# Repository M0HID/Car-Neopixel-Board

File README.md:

# L12

A WLED controller for automotive use, in a small, compact form factor!
<!--  -->
(Check out WLED [here](https://github.com/wled/WLED)!)
## ⚙️ Features:
- < 50x50mm total footprint
- Onboard ESP32
- USB-C for both power and flashing
- JTAG pins broken out
- 4 sets of outputs for 4 seperate strips
- Onboard XL4015 buck converter to convert 12V -> 5V

## 🔧 Installation:
1. In a web browser, open https://install.wled.me/
2. Bridge the `boot` solder jumper using a paperclip, then plug it into your computer
3. Press `install` on the webpage, select the ESP32 Device, and follow the instructions there!

## 📷 Gallery
Check out the PCB on [KiCanvas](https://kicanvas.org/?github=https%3A%2F%2Fgithub.com%2FM0HID%2FCar-Neopixel-Board)!
| Description | Image |
|------------|--------|
| PCB Front |  |
|||
| PCB Back |  |
||
| Board full |  |

## 🔢 BOM
The boards are designed so that one can be installed in all 4 doors of the car, with the final one going in the dashboard as the 'Master' controller

### Capacitors

| Item | Quantity x5 | Part Number | Supplier / Link | Price |
|------|------------|------------|----------------|-------|
| 100 nF capacitor | 3 | C1591 | [link](https://www.lcsc.com/product-detail/C1591.html) | 0.26 |
| 1 µF capacitor | 3 | C15849 | [link](https://www.lcsc.com/product-detail/C15849.html) | 0.25 |
| 22 µF capacitor | 2 | C86295 | [link](https://www.lcsc.com/product-detail/C86295.html) | 0.15 |
| 220 µF capacitor | 1 | C125977 | [link](https://www.lcsc.com/product-detail/C125977.html) | 1.04 |
| 330 µF capacitor | 1 | C249985 | [link](https://www.lcsc.com/product-detail/C249985.html) | 1.57 |

### Resistors

| Item | Quantity x5 | Part Number | Supplier / Link | Price |
|------|------------|------------|----------------|-------|
| 5.1 kΩ resistor | 2 | C23186 | [link](https://www.lcsc.com/product-detail/C23186.html) | 0.11 |
| 10 kΩ resistor | 1 | C25804 | [link](https://www.lcsc.com/product-detail/C25804.html) | 0.10 |
| 22 Ω resistor | 2 | C23345 | [link](https://www.lcsc.com/product-detail/C23345.html) | 0.10 |
| 62 Ω resistor | 4 | C23222 | [link](https://www.lcsc.com/product-detail/C23222.html) | 0.12 |
| 1 kΩ resistor | 1 | C21190 | [link](https://www.lcsc.com/product-detail/C21190.html) | 0.10 |
| 3.3 kΩ resistor | 1 | C22978 | [link](https://www.lcsc.com/product-detail/C22978.html) | 0.11 |

### Diodes

| Item | Quantity x5 | Part Number | Supplier / Link | Price |
|------|------------|------------|----------------|-------|
| SS54 Schottky diode | 3 | C22452 | [link](https://www.lcsc.com/product-detail/C22452.html) | 0.87 |

### Inductors

| Item | Quantity x5 | Part Number | Supplier / Link | Price |
|------|------------|------------|----------------|-------|
| APH1265 inductor | 1 | C5349639 | [link](https://www.lcsc.com/product-detail/C5349639.html) | 2.00 |

### Connectors

| Item | Quantity x5 | Part Number | Supplier / Link | Price |
|------|------------|------------|----------------|-------|
| USB Type-C port | 1 | C165948 | [link](https://www.lcsc.com/product-detail/C165948.html) | 0.88 |
| 2-pin terminal block | 4 | C709041 | [link](https://www.lcsc.com/product-detail/C709041.html) | 3.67 |

### ICs / Modules

| Item | Quantity x5 | Part Number | Supplier / Link | Price |
|------|------------|------------|----------------|-------|
| Level shifter | 1 | C2675672 | [link](https://www.lcsc.com/product-detail/C2675672.html) | 5.73 |
| Buck converter | 1 | C51661 | [link](https://www.lcsc.com/product-detail/C51661.html) | 3.27 |
| Voltage regulator | 1 | C6186 | [link](https://www.lcsc.com/product-detail/C6186.html) | 0.83 |
| ESP32 module | 1 | C2913199 | [link](https://www.lcsc.com/product-detail/C2913199.html) | 25.97 |

### LEDs

| Item | Quantity | Supplier / Link | Price | Notes |
|------|----------|----------------|-------|-------|
| Full Colors 90 cm LED strip | 4 | [link](https://www.aliexpress.com/item/1005004940479033.html) | 28.32 |  |
| Full Colors 110 cm LED strip | 1 | [link](https://www.aliexpress.com/item/1005004940479033.html) | 7.71 |  |
| Full Colors LED strip pack (alternative) | 6 | – | 34.50 | Includes 4×75 cm, 1×90 cm, 1×25 cm (driver side dashboard) |

### PCB (JLCPCB)

| Item | Quantity | Supplier / Link | Price | Notes |
|------|----------|----------------|-------|-------|
| PCB | 5 | [JLCPCB](https://jlcpcb.com) | 3.50 | Standard options for 2-layer board |

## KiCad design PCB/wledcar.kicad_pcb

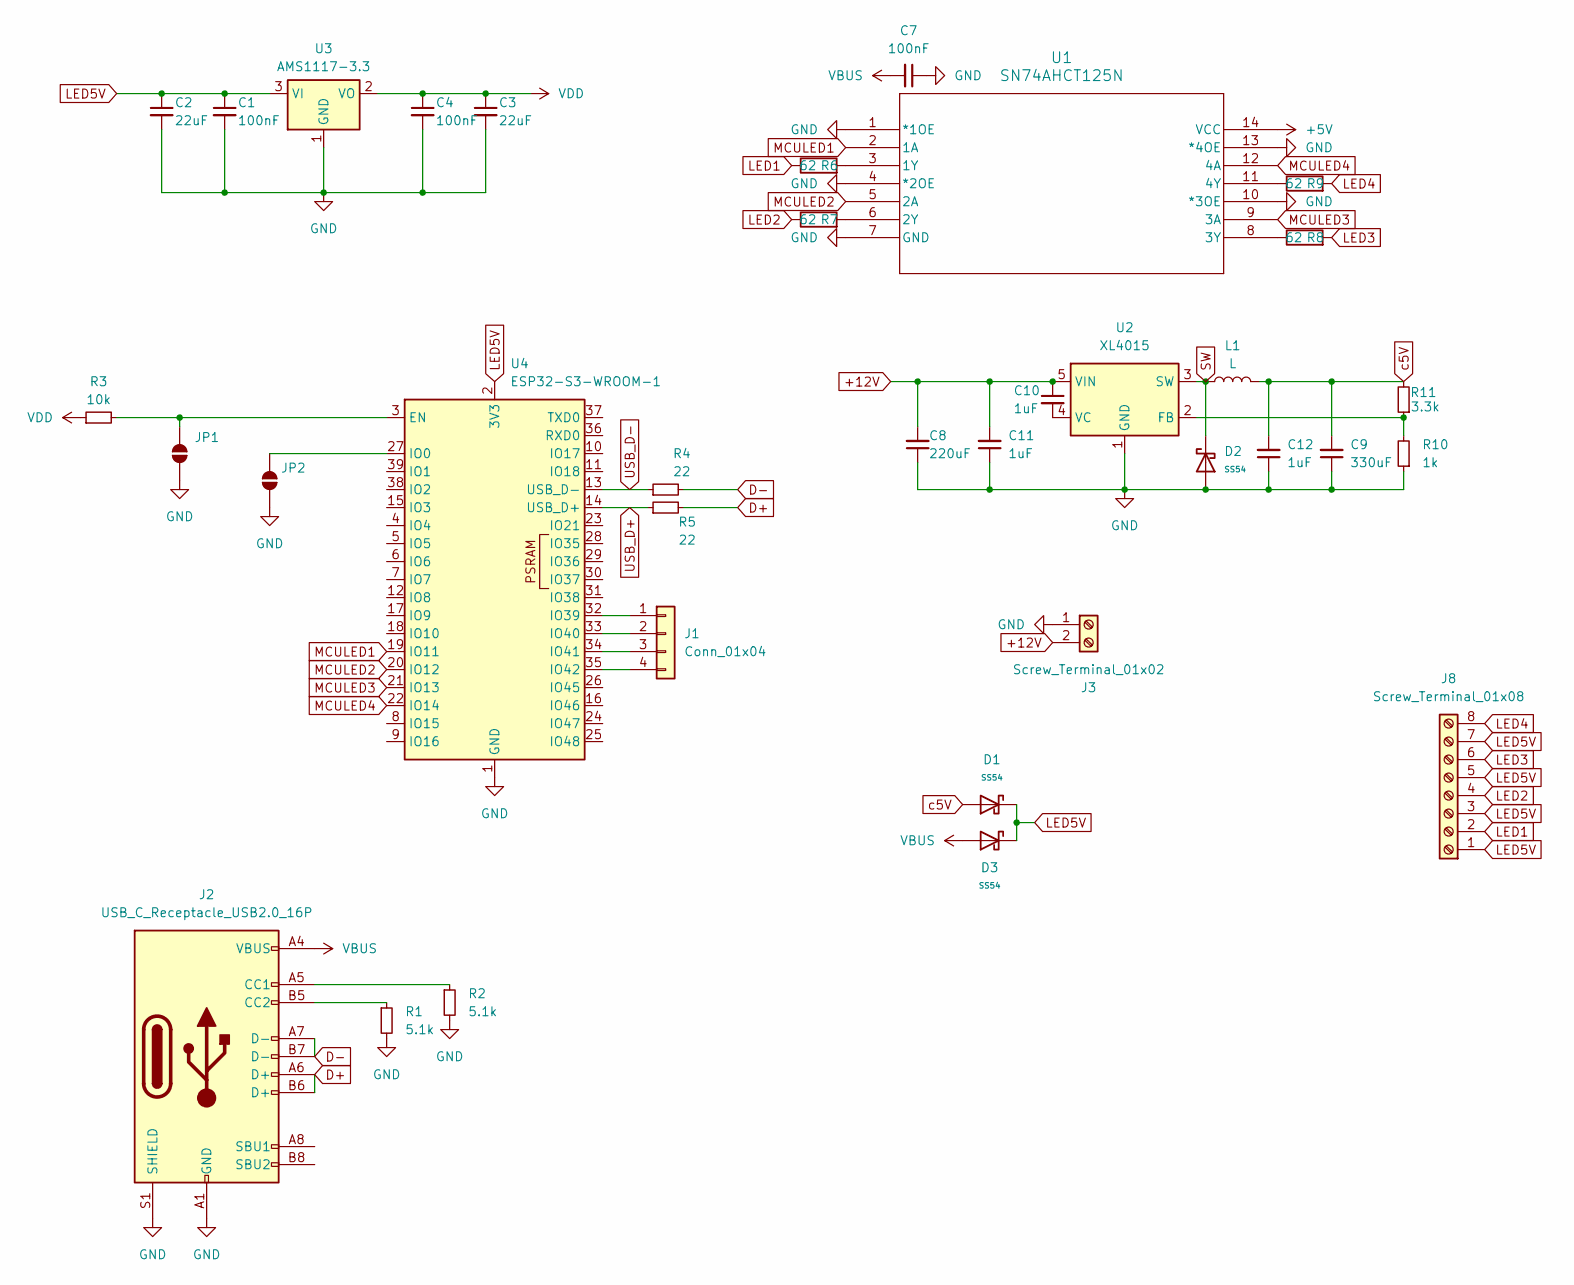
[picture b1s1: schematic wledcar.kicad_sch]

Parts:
C1, C4, C7: 100nF; C_0603_1608Metric
C2, C3: 22uF; C_0603_1608Metric
C8: 220uF; C_0603_1608Metric
C9: 330uF; C_0603_1608Metric
C10, C11, C12: 1uF; C_0603_1608Metric
D1, D2, D3: SS54; D_SMA; Forward Voltage (Vf@If) 550mV@5A; Reverse Voltage (Vr) 40V; Part SS54; LCSC C22452
J1: Conn_01x04; PinHeader_1x04_P1.27mm_Vertical
J2: USB_C_Receptacle_USB2.0_16P; USB_C_Receptacle_HRO_TYPE-C-31-M-12
J3: Screw_Terminal_01x02; TerminalBlock_Phoenix_MKDS-1,5-2-5.08_1x02_P5.08mm_Horizont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
J8: Screw_Terminal_01x08; TerminalBlock_Phoenix_MKDS-3-8-5.08_1x08_P5.08mm_Horizontal
JP1, JP2: SJ2_OPEN; SolderJumper-2_P1.3mm_Open_RoundedPad1.0x1.5mm
L1: L; L_APV_APH1265
R1, R2: 5.1k; R_0603_1608Metric
R3: 10k; R_0603_1608Metric
R4, R5: 22; R_0603_1608Metric
R6, R7, R8, R9: 62; R_0603_1608Metric
R10: 1k; R_0603_1608Metric
R11: 3.3k; R_0603_1608Metric
U1: SN74AHCT125N; SOIC-14_3.9x8.7mm_P1.27mm
U2: XL4015; TO-263-5_TabPin3
U3: AMS1117-3.3; SOT-223-3_TabPin2
U4: ESP32-S3-WROOM-1

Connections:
+5V: U1.14 (VCC)
+12V: C8.2, C10.1, C11.2, J3.2, U2.5 (VIN)
D+: J2.A6 (D+), J2.B6 (D+), R5.2
D-: J2.A7 (D-), J2.B7 (D-), R4.2
GND: C1.2, C2.2, C3.2, C4.2, C7.1, C8.1, C9.1, C11.1, C12.1, D2.2, J2.A1 (GND), J2.A12 (GND), J2.B1 (GND), J2.B12 (GND), J2.S1 (SHIELD), J3.1, JP1.1 (A), JP2.1 (A), R1.2, R2.2, R10.1, U1.1 (*1OE), U1.4 (*2OE), U1.7 (GND), U1.10 (*3OE), U1.13 (*4OE), U2.1 (GND), U3.1 (GND), U4.1 (GND), U4.40 (GND), U4.41 (GND)
LED1: J8.2, R6.1
LED2: J8.4, R7.1
LED3: J8.6, R8.2
LED4: J8.8, R9.2
LED5V: C1.1, C2.1, D1.1, D3.1, J8.1, J8.3, J8.5, J8.7, U3.3 (VI), U4.2 (3V3)
MCULED1: U1.2 (1A), U4.19 (IO11)
MCULED2: U1.5 (2A), U4.20 (IO12)
MCULED3: U1.9 (3A), U4.21 (IO13)
MCULED4: U1.12 (4A), U4.22 (IO14)
unnamed: J1.1, U4.32 (IO39)
unnamed: J1.2, U4.33 (IO40)
unnamed: J1.3, U4.34 (IO41)
unnamed: J1.4, U4.35 (IO42)
unnamed: J2.A5 (CC1), R2.1
unnamed: J2.B5 (CC2), R1.1
unnamed: JP1.2 (B), R3.2, U4.3 (EN)
unnamed: JP2.2 (B), U4.27 (IO0)
unnamed: R6.2, U1.3 (1Y)
unnamed: R7.2, U1.6 (2Y)
unnamed: R8.1, U1.8 (3Y)
unnamed: R9.1, U1.11 (4Y)
unnamed: R10.2, R11.1, U2.2 (FB)
unnamed: C10.2, U2.4 (VC)
SW: D2.1, L1.1, U2.3 (SW)
USB_D+: R5.1, U4.14 (USB_D+)
USB_D-: R4.1, U4.13 (USB_D-)
VBUS: C7.2, D3.2, J2.A4 (VBUS), J2.A9 (VBUS), J2.B4 (VBUS), J2.B9 (VBUS)
VDD: C3.1, C4.1, R3.1, U3.2 (VO)
c5V: C9.2, C12.2, D1.2, L1.2, R11.2

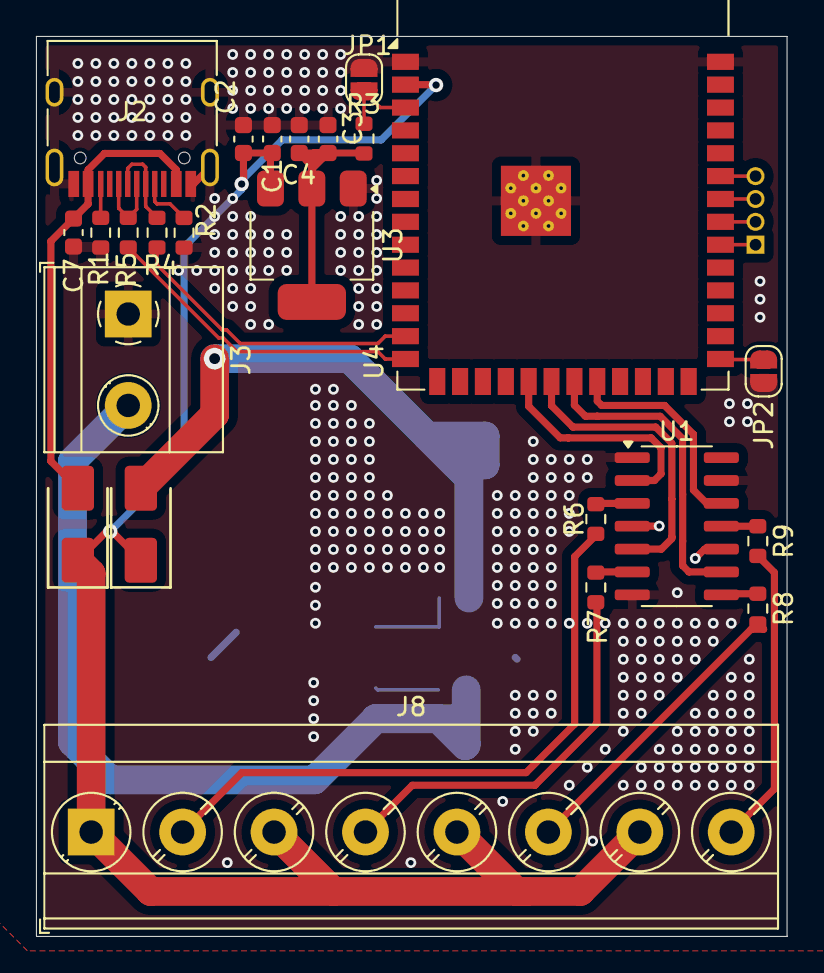
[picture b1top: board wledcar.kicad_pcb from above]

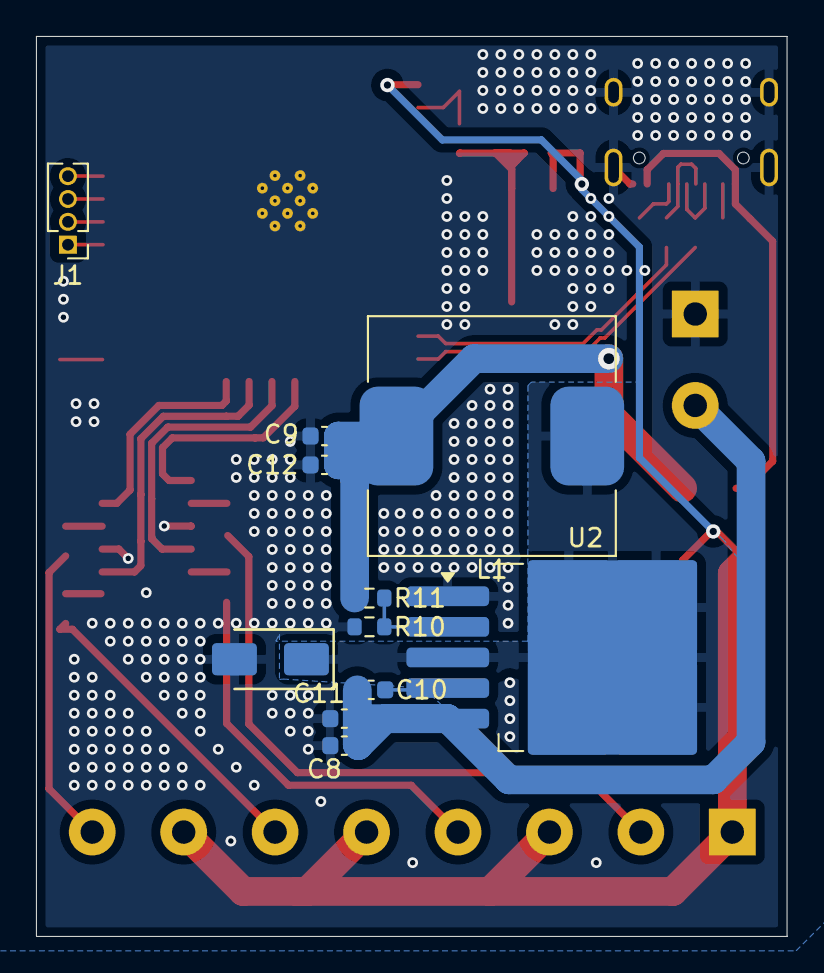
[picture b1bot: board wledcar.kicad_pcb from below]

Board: 2 copper layers, 41.7 x 50.0 mm, 35 parts (11 on the bottom side), 33 nets.

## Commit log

2025-11-21 add initial schem
2025-12-01 redid the whole pcb modified: wledcar.kicad_pcb modified: wledcar.kicad_pro modified: wledcar.kicad_sch
2025-12-02 did some cyaoing modified: wledcar.kicad_pcb modified: wledcar.kicad_pro modified: wledcar.kicad_sch
2025-12-03 moar update modified: wledcar.kicad_pcb modified: wledcar.kicad_pro modified: wledcar.kicad_sch
2025-12-03 few edits modified: wledcar.kicad_pcb
2025-12-05 add more imgs
2025-12-05 renamed: 2025-11-21_18-39-34.kicad_sym -> PCB/2025-11-21_18-39-34.kicad_sym renamed: 2060-452_998-404.step -> PCB/2060-452_998-404.step renamed: WAGO_2060-452_998-404.kicad_mod -> PCB/WAGO_2060-452_9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
2025-12-05 new file: Production/wledcar.zip
